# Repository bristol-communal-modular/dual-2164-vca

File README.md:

# Dual VCA

A Dual VCA based in part on Mutable Instruments Veils.

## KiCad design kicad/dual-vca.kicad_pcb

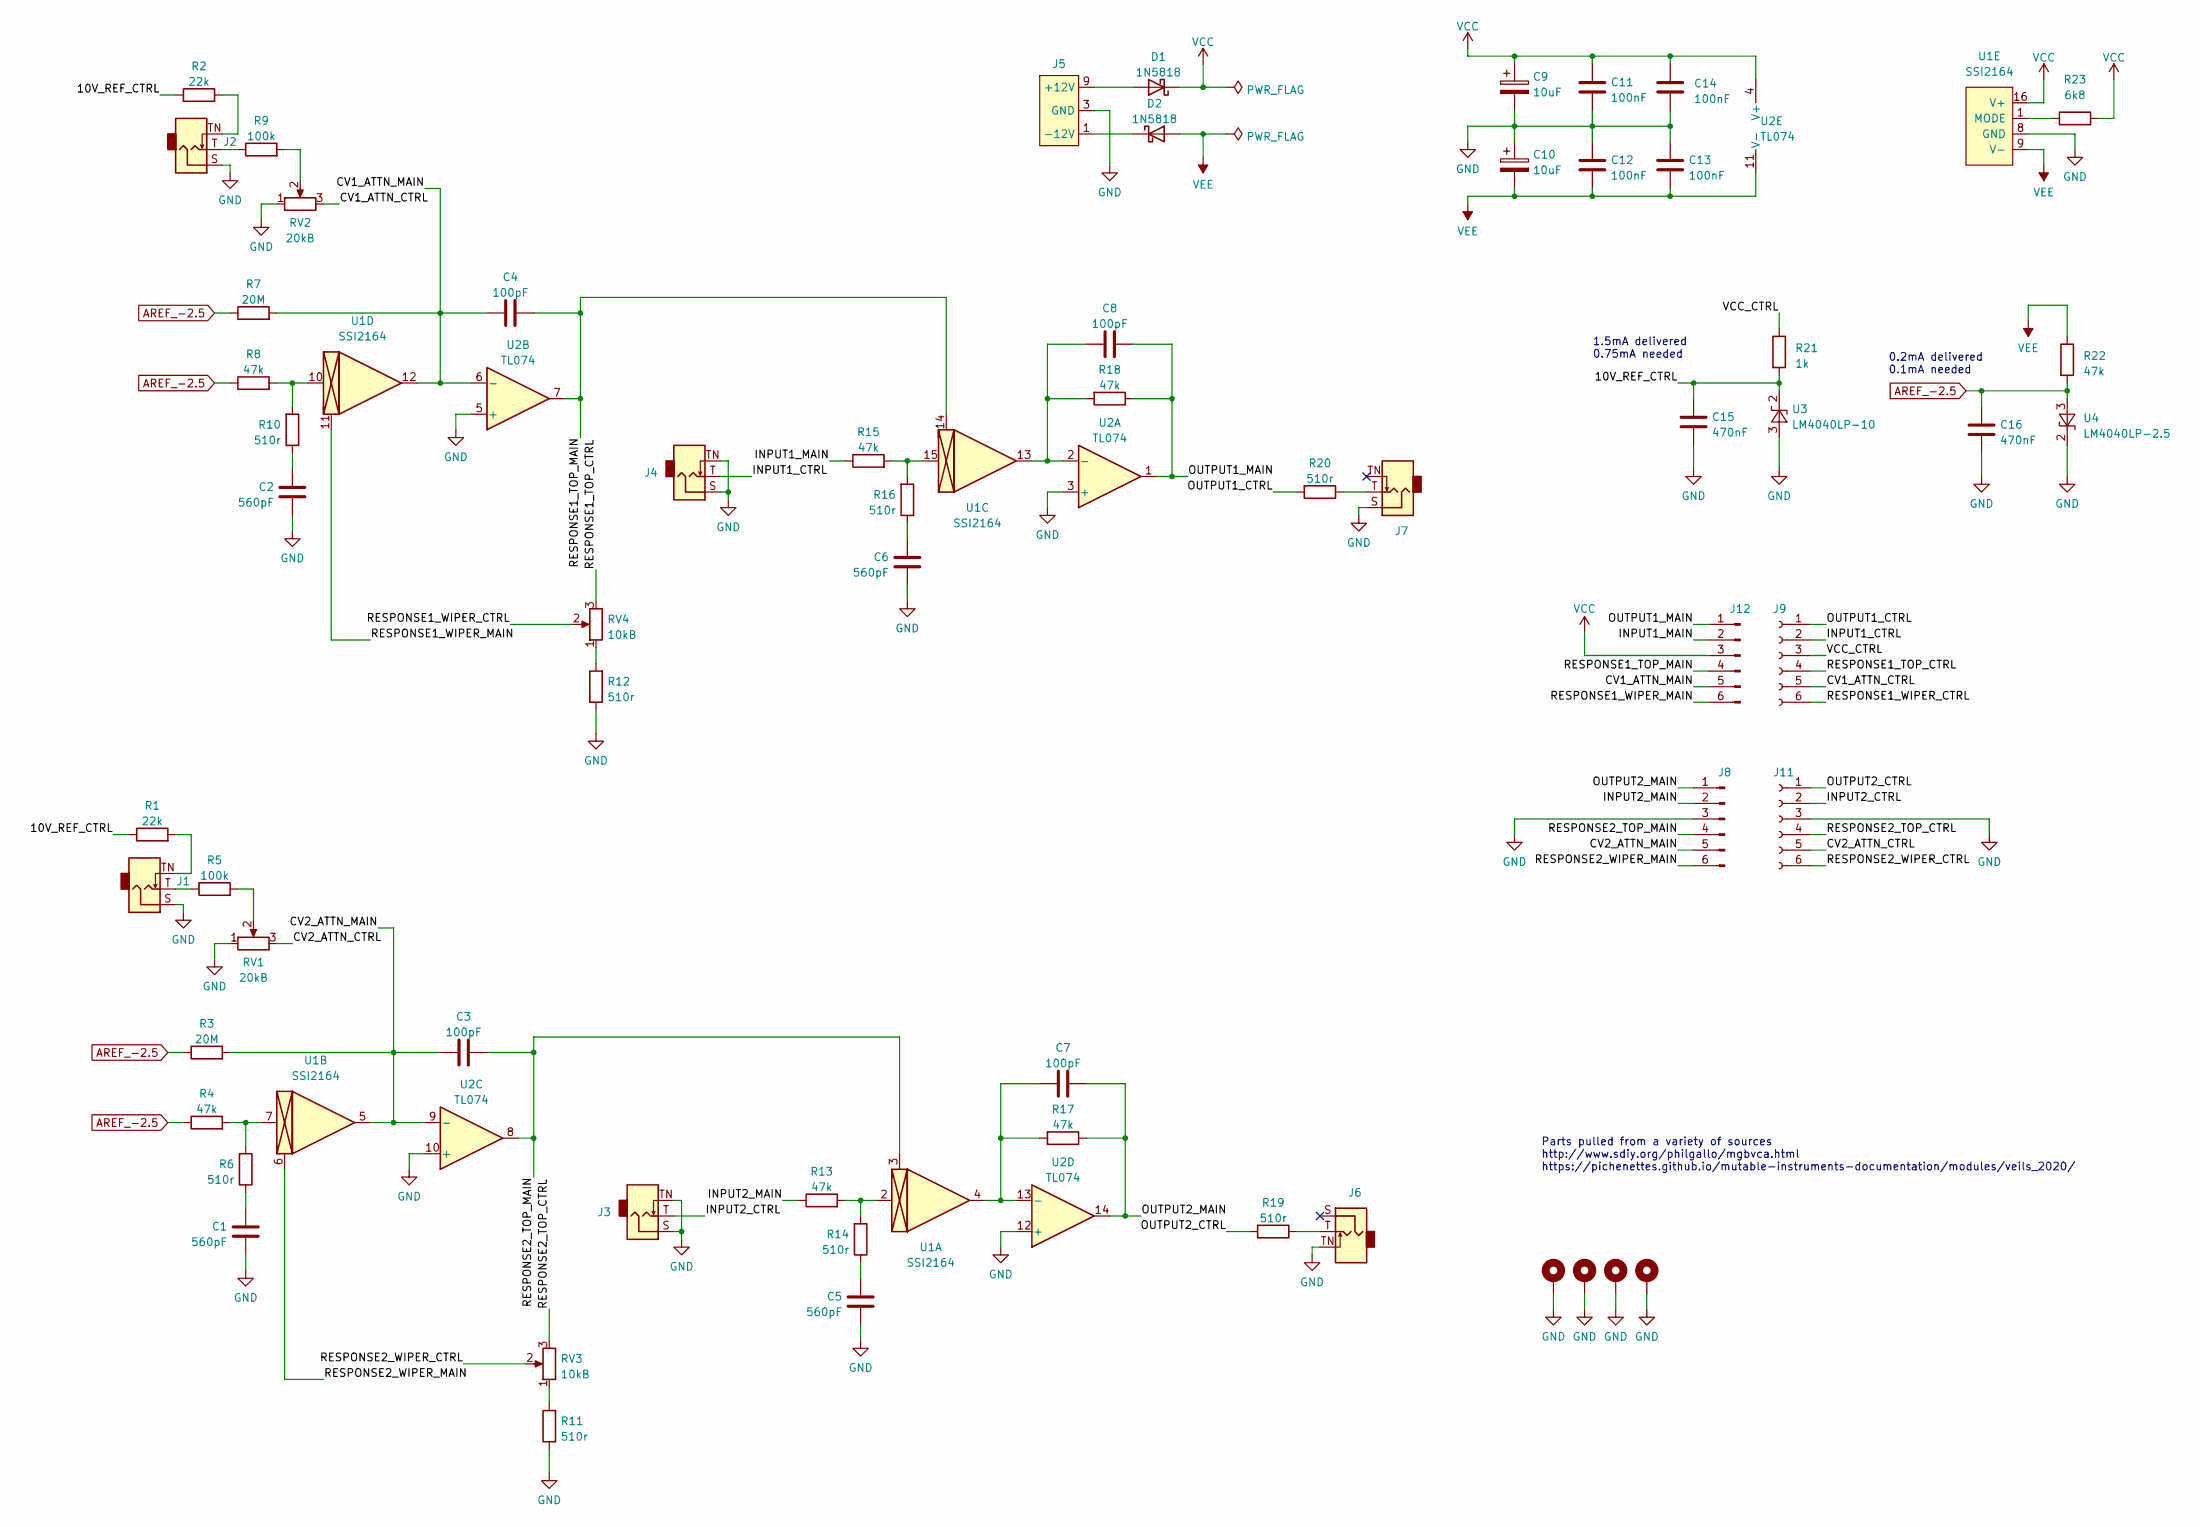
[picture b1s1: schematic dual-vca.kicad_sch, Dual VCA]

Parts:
C1, C2, C5, C6: 560pF; C_Rect_L7.0mm_W2.5mm_P5.00mm; Tolerance 5%
C3, C4, C7, C8: 100pF; C_Rect_L7.0mm_W2.5mm_P5.00mm; Tolerance 5%
C9, C10: 10uF; CP_Radial_D5.0mm_P2.00mm; Tolerance 20%; Voltage 50v
C11, C12, C13, C14: 100nF; C_Rect_L7.0mm_W2.5mm_P5.00mm; Tolerance 5%
C15, C16: 470nF; C_Rect_L7.0mm_W2.5mm_P5.00mm; Tolerance 5%
D1, D2: 1N5818; D_DO-41_SOD81_P10.16mm_Horizontal
H1, H2, H3, H4: MountingHole_Pad; MountingHole_3.2mm_M3_DIN965_Pad
J1, J2, J3, J4, J6, J7: Eurorack Mono Jack; Jack_3.5mm_QingPu_WQP-PJ398SM_Vertical; mpn WQP-WQP518MA
J5: Eurorack Power Small; Eurorack_PowerHeader_2x05_P2.54mm_Shrouded
J8, J12: Conn_01x06_Pin; PinHeader_1x06_P2.54mm_Vertical
J9, J11: Conn_01x06_Socket; PinSocket_1x06_P2.54mm_Vertical
R1, R2: 22k; R_Axial_DIN0207_L6.3mm_D2.5mm_P10.16mm_Horizontal; Tolerance 1%
R3, R7: 20M; R_Axial_DIN0207_L6.3mm_D2.5mm_P10.16mm_Horizontal; Tolerance 1%
R4, R8, R13, R15, R17, R18, R22: 47k; R_Axial_DIN0207_L6.3mm_D2.5mm_P10.16mm_Horizontal; Tolerance 1%
R5, R9: 100k; R_Axial_DIN0207_L6.3mm_D2.5mm_P10.16mm_Horizontal; Tolerance 1%
R6, R10, R11, R12, R14, R16, R19, R20: 510r; R_Axial_DIN0207_L6.3mm_D2.5mm_P10.16mm_Horizontal; Tolerance 1%
R21: 1k; R_Axial_DIN0207_L6.3mm_D2.5mm_P10.16mm_Horizontal; Tolerance 1%
R23: 6k8; R_Axial_DIN0207_L6.3mm_D2.5mm_P10.16mm_Horizontal; Tolerance 1%
RV1, RV2: 20kB; Potentiometer_Alpha_RD901F-40-00D_Single_Vertical
RV3, RV4: 10kB; Potentiometer_Alpha_RD901F-40-00D_Single_Vertical
U1: SSI2164; DIP-16_W7.62mm_Socket
U2: TL074; DIP-14_W7.62mm_Socket
U3: LM4040LP-10; TO-92_Inline_Wide
U4: LM4040LP-2.5; TO-92_Inline_Wide

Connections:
/10V_REF_CTRL: C15.1, R1.1, R2.1, R21.2, U3.2 (K)
/CV1_ATTN_CTRL: J9.5, RV2.3
/CV1_ATTN_MAIN: C4.1, J12.5, R7.2, U1.12, U2.6 (-)
/CV2_ATTN_CTRL: J11.5, RV1.3
/CV2_ATTN_MAIN: C3.1, J8.5, R3.2, U1.5, U2.9 (-)
/INPUT1_CTRL: J4.T, J9.2
/INPUT1_MAIN: J12.2, R15.1
/INPUT2_CTRL: J3.T, J11.2
/INPUT2_MAIN: J8.2, R13.1
/OUTPUT1_CTRL: J9.1, R20.2
/OUTPUT1_MAIN: C8.2, J12.1, R18.1, U2.1
/OUTPUT2_CTRL: J11.1, R19.2
/OUTPUT2_MAIN: C7.2, J8.1, R17.1, U2.14
/RESPONSE1_TOP_CTRL: J9.4, RV4.3
/RESPONSE1_TOP_MAIN: C4.2, J12.4, U1.14, U2.7
/RESPONSE1_WIPER_CTRL: J9.6, RV4.2
/RESPONSE1_WIPER_MAIN: J12.6, U1.11
/RESPONSE2_TOP_CTRL: J11.4, RV3.3
/RESPONSE2_TOP_MAIN: C3.2, J8.4, U1.3, U2.8
/RESPONSE2_WIPER_CTRL: J11.6, RV3.2
/RESPONSE2_WIPER_MAIN: J8.6, U1.6
/VCC_CTRL: J9.3, R21.1
AREF_-2.5: C16.1, R3.1, R4.1, R7.1, R8.1, R22.2, U4.3 (A)
GND: C1.1, C2.1, C5.1, C6.1, C9.2, C10.1, C11.2, C12.1, C13.1, C14.1, C15.2, C16.2, H1.1, H2.1, H3.1, H4.1, J1.S, J2.S, J3.S, J3.TN, J4.S, J4.TN, J5.3 (GND), J5.4 (GND), J5.5 (GND), J5.6 (GND), J5.7 (GND), J5.8 (GND), J6.TN, J7.S, J8.3, J11.3, R11.1, R12.1, RV1.1, RV2.1, U1.8 (GND), U2.3 (+), U2.5 (+), U2.10 (+), U2.12 (+), U3.3 (A), U4.2 (K)
unnamed: C1.2, R6.1
unnamed: C2.2, R10.1
unnamed: C5.2, R14.1
unnamed: C6.2, R16.1
unnamed: D1.2 (A), J5.9 (+12V), J5.10 (+12V)
unnamed: D2.1 (K), J5.1 (-12V), J5.2 (-12V)
unnamed: J1.T, R5.1
unnamed: J1.TN, R1.2
unnamed: J2.T, R9.1
unnamed: J2.TN, R2.2
unnamed: J6.T, R19.1
unnamed: J7.T, R20.1
unnamed: R4.2, R6.2, U1.7
unnamed: R5.2, RV1.2
unnamed: R9.2, RV2.2
unnamed: R8.2, R10.2, U1.10
unnamed: R11.2, RV3.1
unnamed: R12.2, RV4.1
unnamed: R13.2, R14.2, U1.2
unnamed: R15.2, R16.2, U1.15
unnamed: R23.1, U1.1 (MODE)
unnamed: C8.1, R18.2, U1.13, U2.2 (-)
unnamed: C7.1, R17.2, U1.4, U2.13 (-)
VCC: C9.1, C11.1, C14.2, D1.1 (K), J12.3, R23.2, U1.16 (V+), U2.4 (V+)
VEE: C10.2, C12.2, C13.2, D2.2 (A), R22.1, U1.9 (V-), U2.11 (V-)

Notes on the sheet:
Parts pulled from a variety of sources http://www.sdiy.org/philgallo/mgbvca.html https://pichenettes.github.io/mutable-instruments-documentation/modules/veils_2020/
0.2mA delivered 0.1mA needed
1.5mA delivered 0.75mA needed

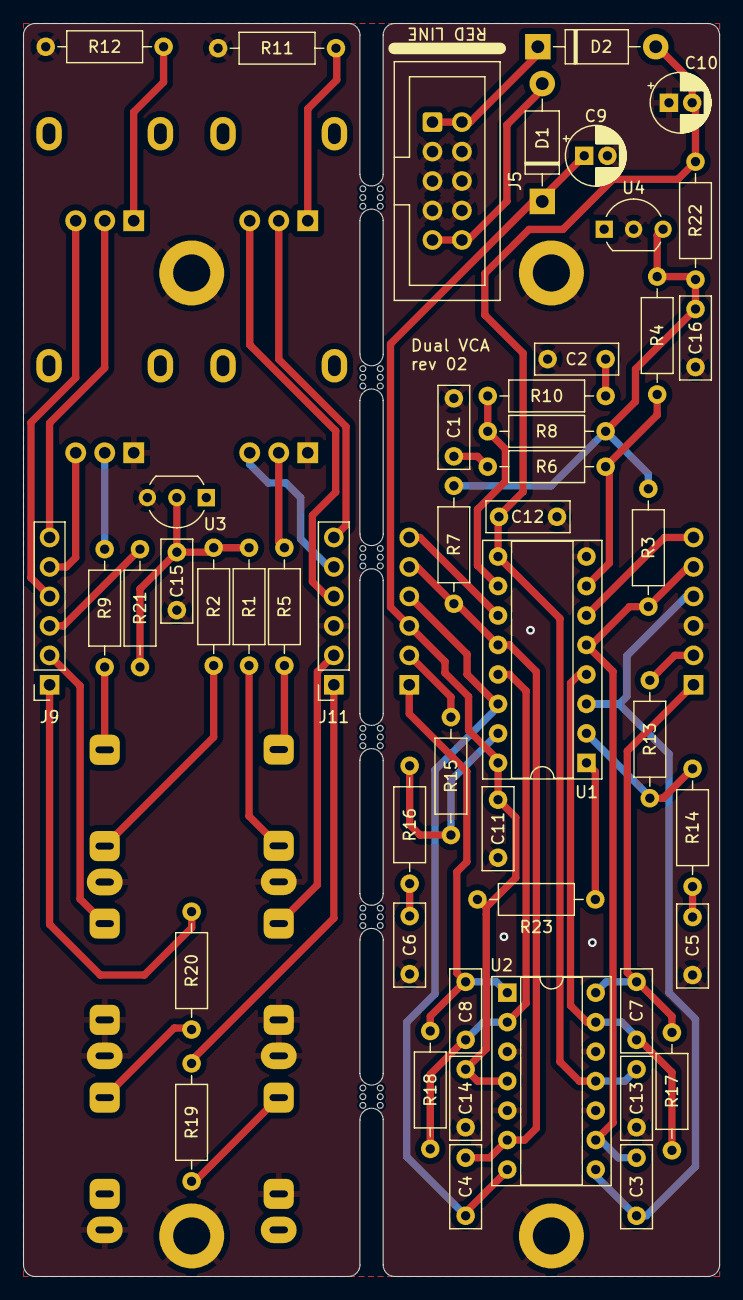
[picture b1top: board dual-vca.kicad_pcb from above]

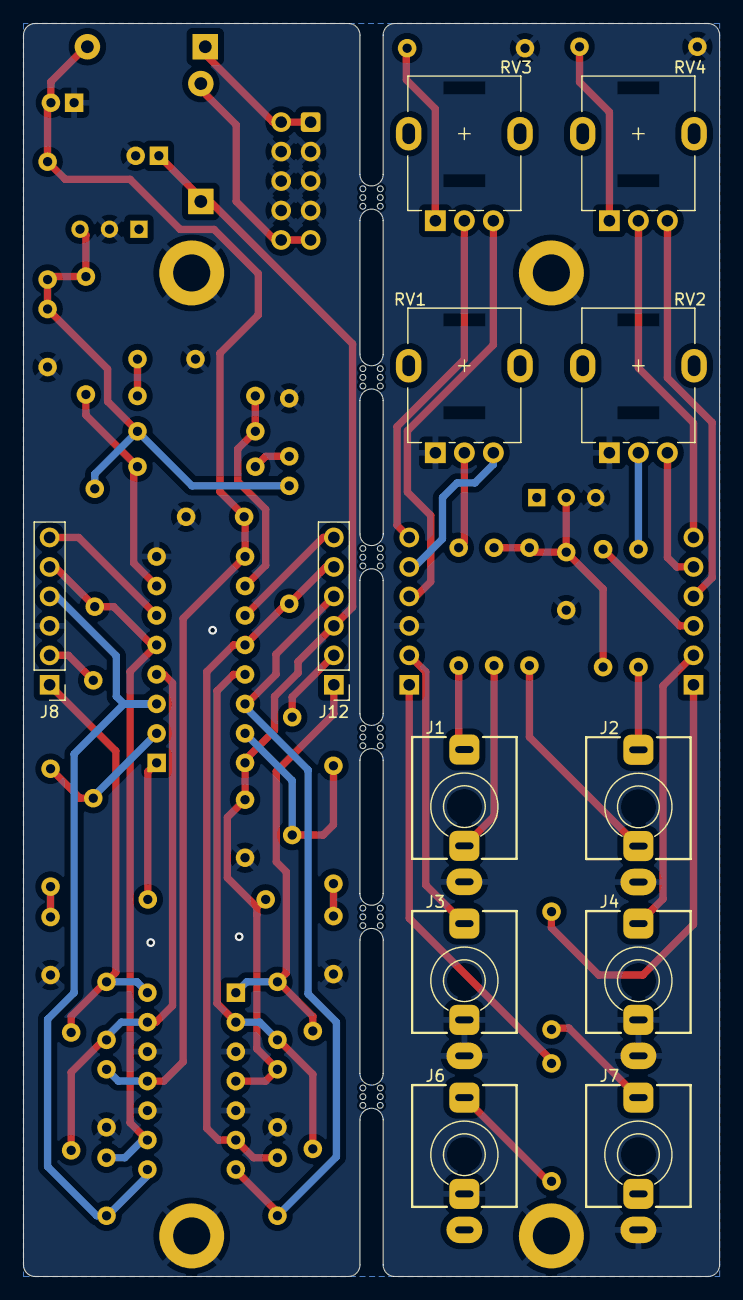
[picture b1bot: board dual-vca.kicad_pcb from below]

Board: 2 copper layers, 60.0 x 108.0 mm, 70 parts (12 on the bottom side), 49 nets.

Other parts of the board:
mouse-bite-2mm-slot, mouse-bite-2mm-slot#2, mouse-bite-2mm-slot#3, mouse-bite-2mm-slot#4, mouse-bite-2mm-slot#5, mouse-bite-2mm-slot#6: VAL**; mouse-bite-2mm-slot

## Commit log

2023-10-23 Adding beginnings of panel files and routed more of the pcb
2023-11-12 Finishing routing PCBs
2024-07-04 Fixes for revision 2
2024-07-04 Adding panel
2024-07-04 Ignoring new temporary kicad files in git
2024-07-04 Adding rev02 gerbers
2024-07-07 Minor tweaks and tidying

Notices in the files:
kicad/dual-vca.kicad_pcb:
creativecommons.org/licenses/by/4.0
License: CC BY 4.0
